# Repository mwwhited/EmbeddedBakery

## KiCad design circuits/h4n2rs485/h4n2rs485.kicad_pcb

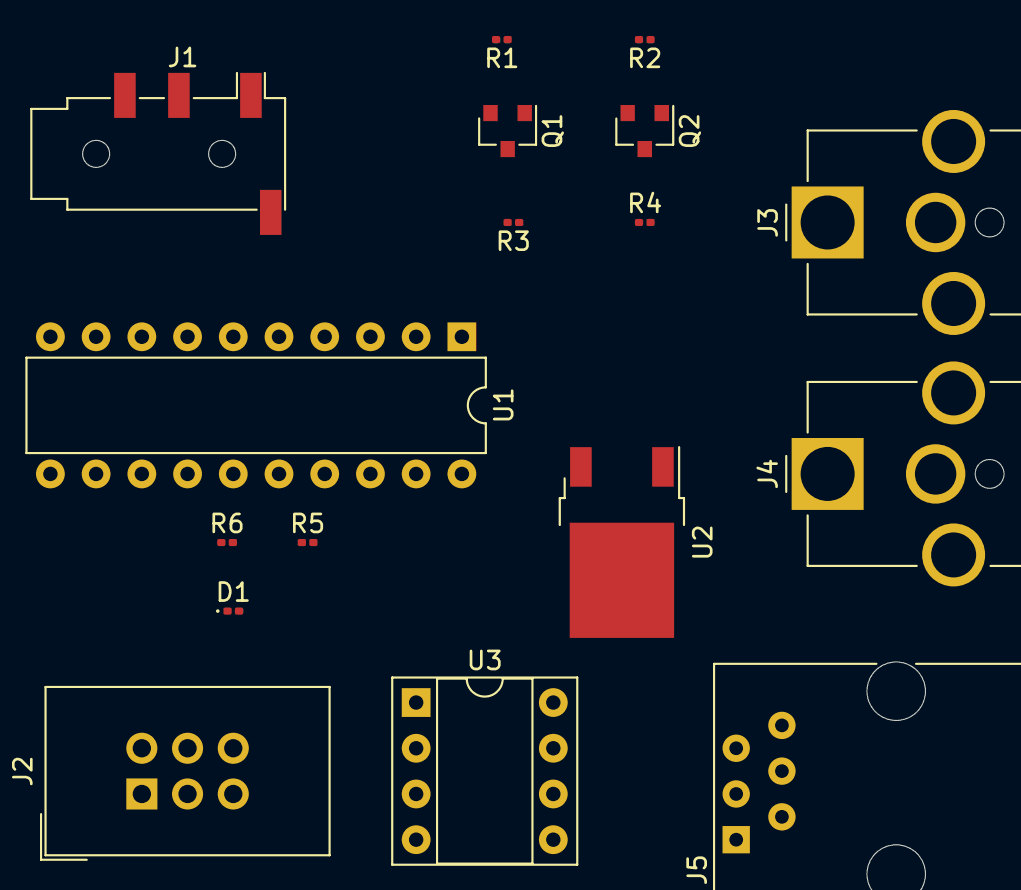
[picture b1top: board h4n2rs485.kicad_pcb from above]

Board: 2 copper layers, 17 parts (0 on the bottom side), 16 nets, no tracks yet.

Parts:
D1: LED; LED_0201_0603Metric
J1: AudioJack4; Jack_3.5mm_PJ320D_Horizontal
J2: AVR-ISP-6; IDC-Header_2x03_P2.54mm_Vertical
J3, J4: Barrel_Jack; BarrelJack_CUI_PJ-063AH_Horizontal_CircularHoles
J5: 6P6C; RJ12_Amphenol_54601
Q1, Q2: BSS138; SOT-23
R1, R2, R3, R4: R 10k; R_0201_0603Metric
R5, R6: R_US; R_0201_0603Metric
U1: ATtiny2313-20PU; DIP-20_W7.62mm
U2: L7805; TO-252-2
U3: MAX485E; DIP-8_W7.62mm_Socket

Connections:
+3V3: J1.S, Q1.1, Q2.1, R1.1, R2.1
+5V: J2.2, J5.2, R3.1, R4.1, R5.1, U1.20, U2.3, U3.8
+12V: J3.1, J4.1, U2.1
GND: D1.1, J1.R2, J2.6, J3.2, J4.2, J5.5, U1.10, U2.2, U3.5
unnamed: D1.2, R6.2
unnamed: J1.R1, Q1.2, R1.2
unnamed: J1.T, Q2.2, R2.2
unnamed: J2.1, U1.18, U3.4
unnamed: J2.3, U1.19
unnamed: J2.4, U1.17, U3.1
unnamed: J2.5, U1.1
unnamed: J5.3, U3.7
unnamed: J5.4, U3.6
unnamed: Q1.3, R3.2, U1.3
unnamed: Q2.3, R4.2, U1.2
unnamed: R5.2, R6.1, U1.16, U3.2, U3.3
